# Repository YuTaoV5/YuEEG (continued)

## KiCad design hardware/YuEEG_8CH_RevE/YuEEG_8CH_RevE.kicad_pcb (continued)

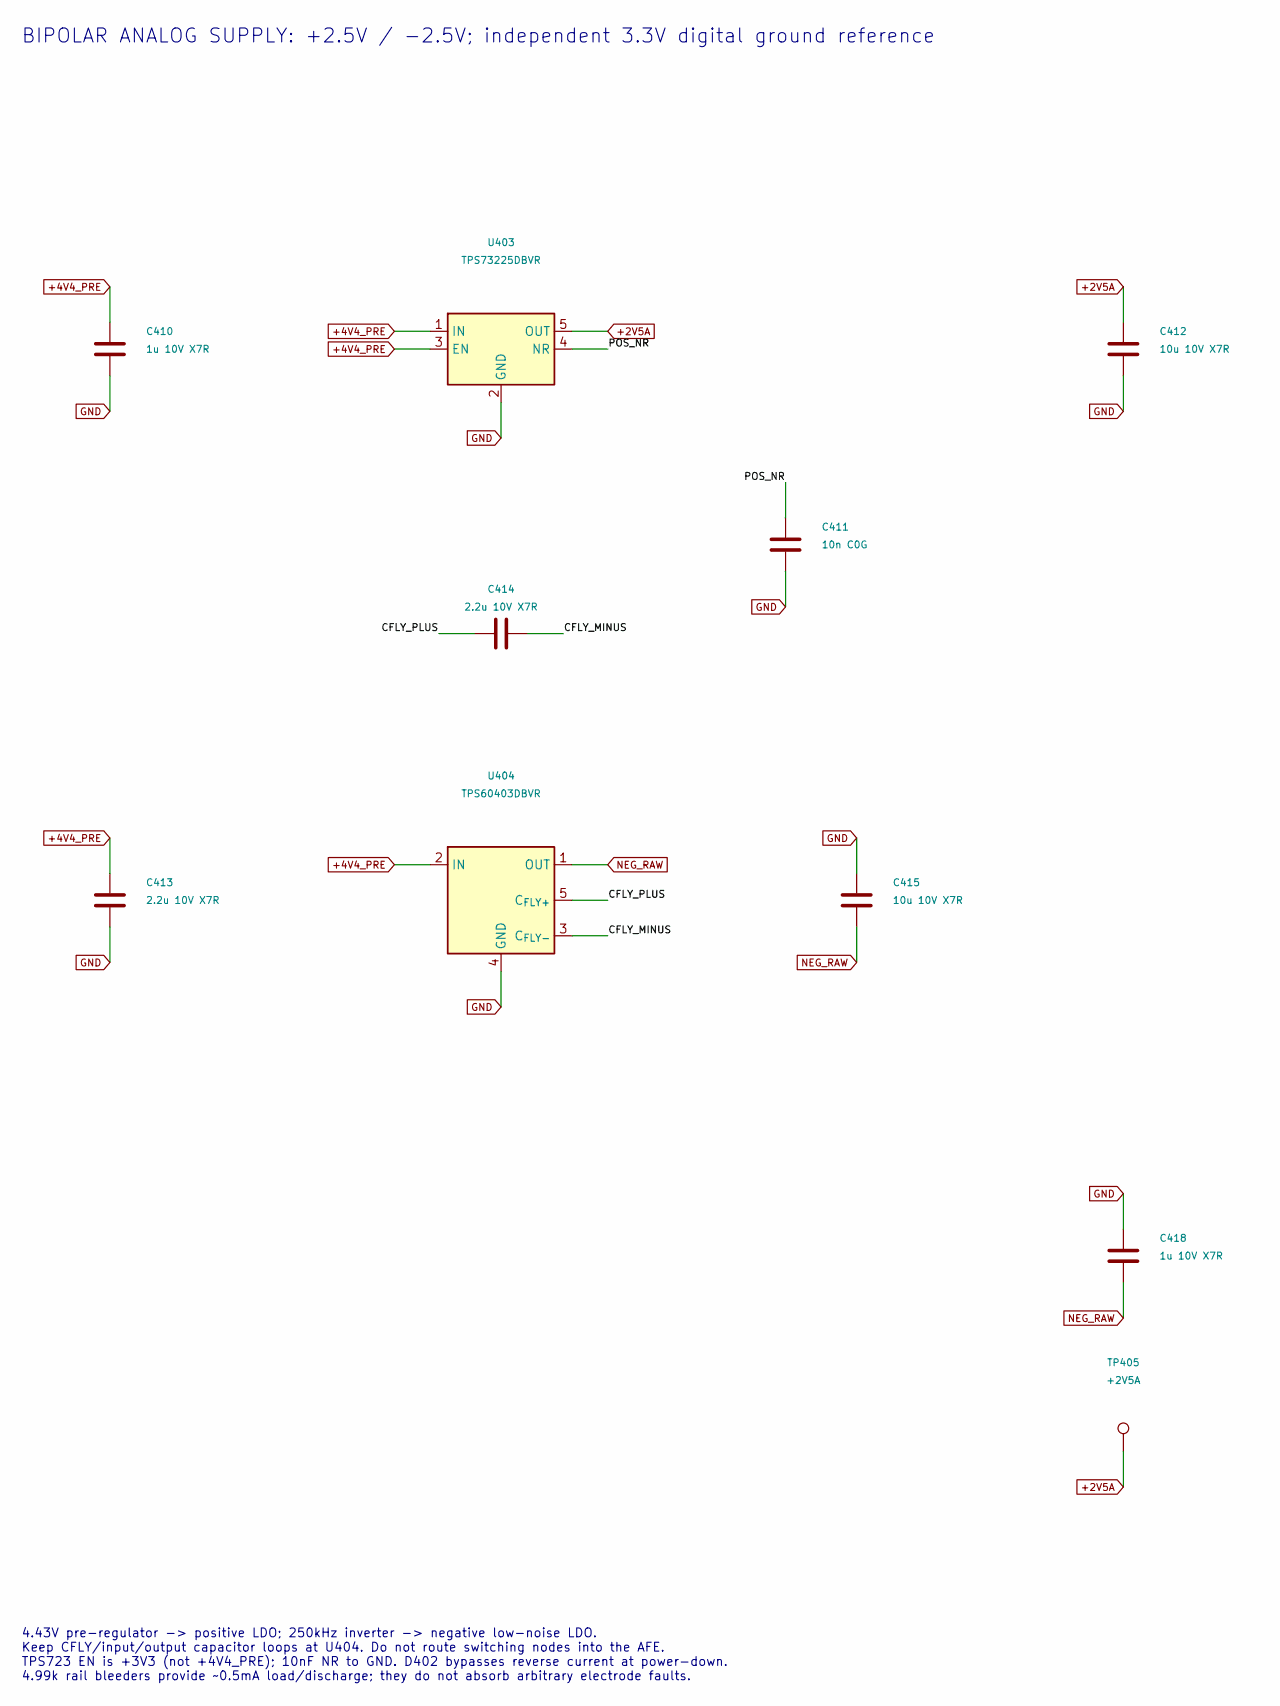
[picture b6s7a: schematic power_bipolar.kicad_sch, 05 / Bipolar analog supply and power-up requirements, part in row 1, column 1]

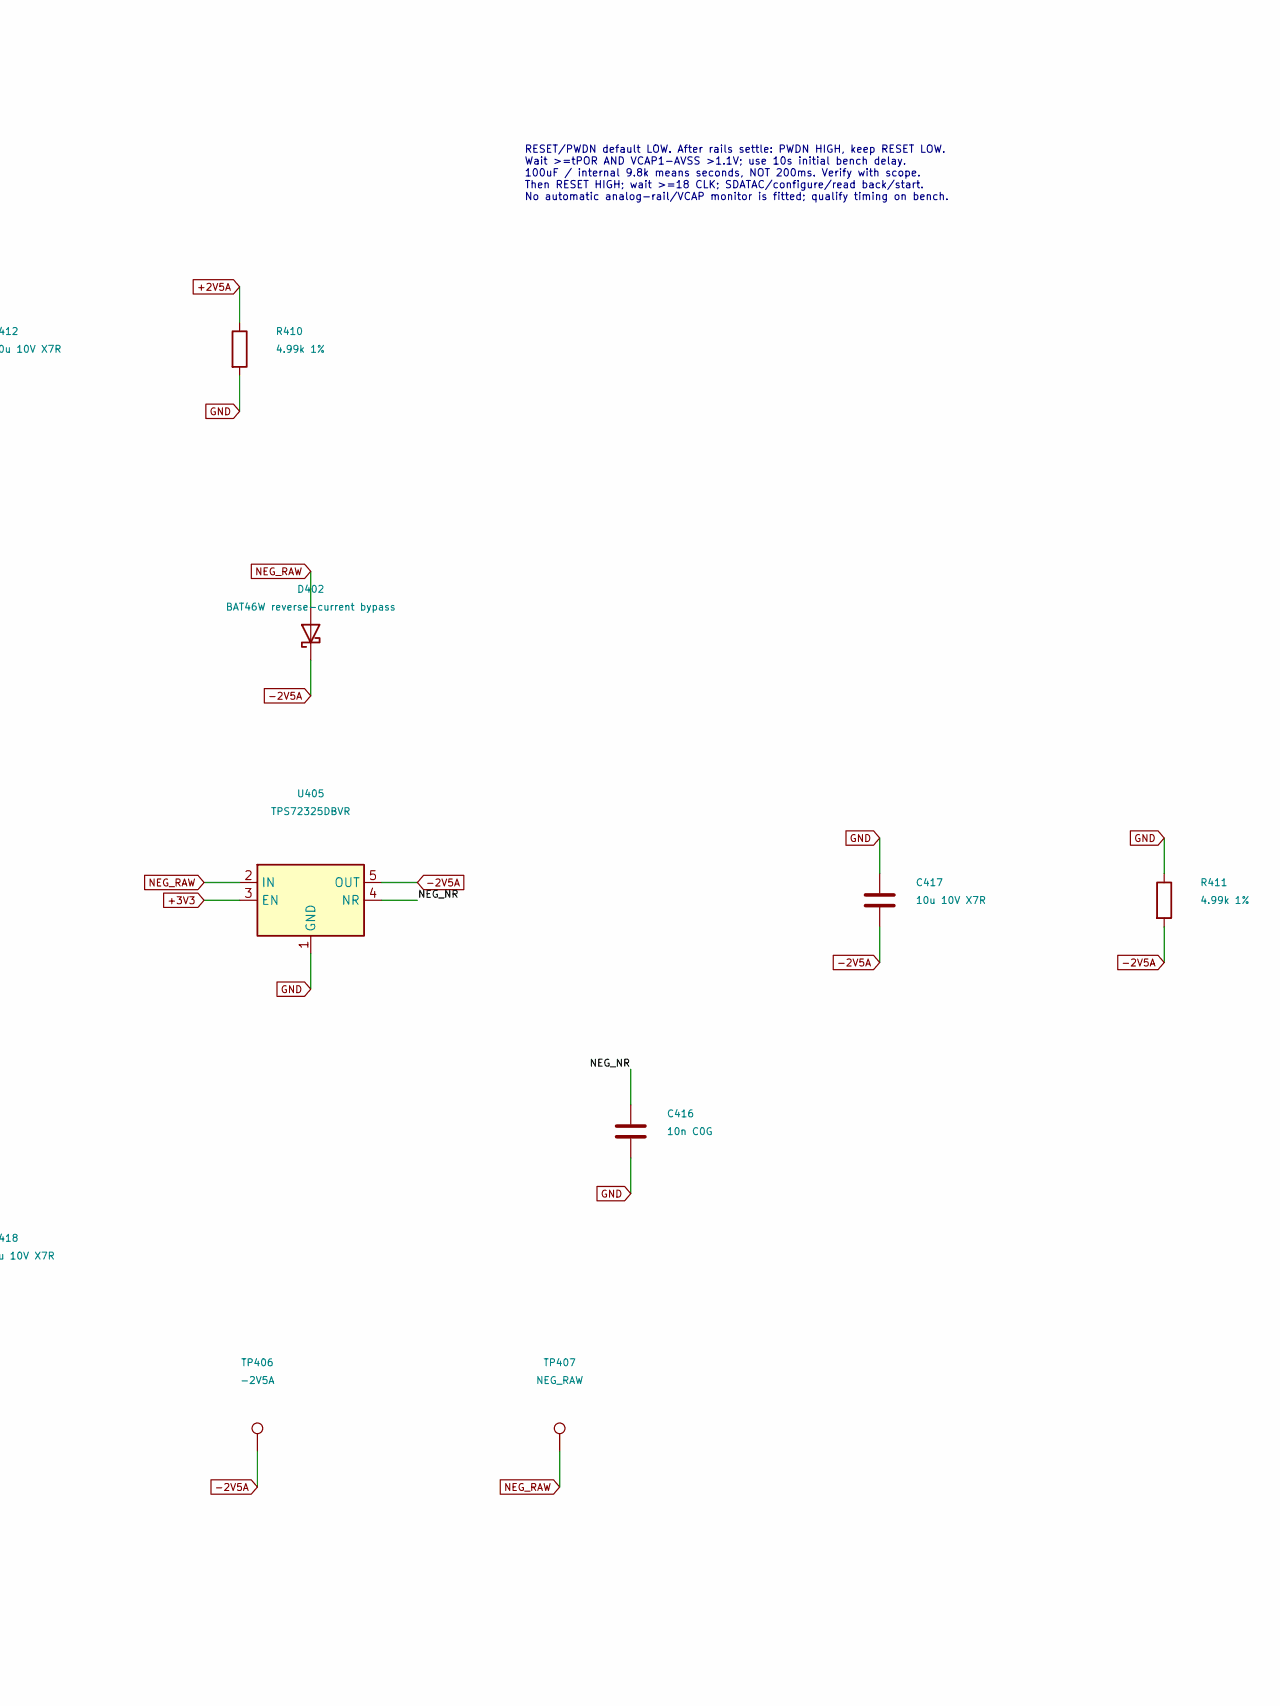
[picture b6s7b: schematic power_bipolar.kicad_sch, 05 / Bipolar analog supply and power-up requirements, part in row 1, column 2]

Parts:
C410, C418: 1u 10V X7R; C_0603_1608Metric
C411, C416: 10n C0G; C_0603_1608Metric
C412, C415, C417: 10u 10V X7R; C_0805_2012Metric
C413, C414: 2.2u 10V X7R; C_0805_2012Metric
D402: BAT46W reverse-current bypass; D_SOD-123
R410, R411: 4.99k 1%; R_0603_1608Metric
TP405: +2V5A; TestPoint_Pad_D1.5mm
TP406: -2V5A; TestPoint_Pad_D1.5mm
TP407: NEG_RAW; TestPoint_Pad_D1.5mm
U403: TPS73225DBVR; SOT-23-5
U404: TPS60403DBVR; SOT-23-5
U405: TPS72325DBVR; SOT-23-5

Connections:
+2V5A: C412.1, R410.1, TP405.1, U403.5 (OUT); also elsewhere on the board
+3V3: U405.3 (EN); also elsewhere on the board
+4V4_PRE: C410.1, C413.1, U403.1 (IN), U403.3 (EN), U404.2 (IN); also elsewhere on the board
-2V5A: C417.2, D402.1 (K), R411.2, TP406.1, U405.5 (OUT); also elsewhere on the board
/05 / Bipolar analog supply/CFLY_MINUS: C414.2, U404.3 (C_{FLY-})
/05 / Bipolar analog supply/CFLY_PLUS: C414.1, U404.5 (C_{FLY+})
/05 / Bipolar analog supply/NEG_NR: C416.1, U405.4 (NR)
/05 / Bipolar analog supply/POS_NR: C411.1, U403.4 (NR)
GND: C410.2, C411.2, C412.2, C413.2, C415.1, C416.2, C417.1, C418.1, R410.2, R411.1, U403.2 (GND), U404.4 (GND), U405.1 (GND); also elsewhere on the board
NEG_RAW: C415.2, C418.2, D402.2 (A), TP407.1, U404.1 (OUT), U405.2 (IN)

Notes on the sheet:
BIPOLAR ANALOG SUPPLY: +2.5V / -2.5V; independent 3.3V digital ground reference
4.43V pre-regulator -> positive LDO; 250kHz inverter -> negative low-noise LDO. Keep CFLY/input/output capacitor loops at U404. Do not route switching nodes into the AFE. TPS723 EN is +3V3 (not +4V4_PRE); 10nF NR to GND. D402 bypasses reverse current at power-down. 4.99k rail bleeders provide ~0.5m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
RESET/PWDN default LOW. After rails settle: PWDN HIGH, keep RESET LOW. Wait >=tPOR AND VCAP1-AVSS >1.1V; use 10s initial bench delay. 100uF / internal 9.8k means seconds, NOT 200ms. Verify with scope. Then RESET HIGH; wait >=18 CLK; SDATAC/configure/read back/start. No automatic analog-rail/VCAP mo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

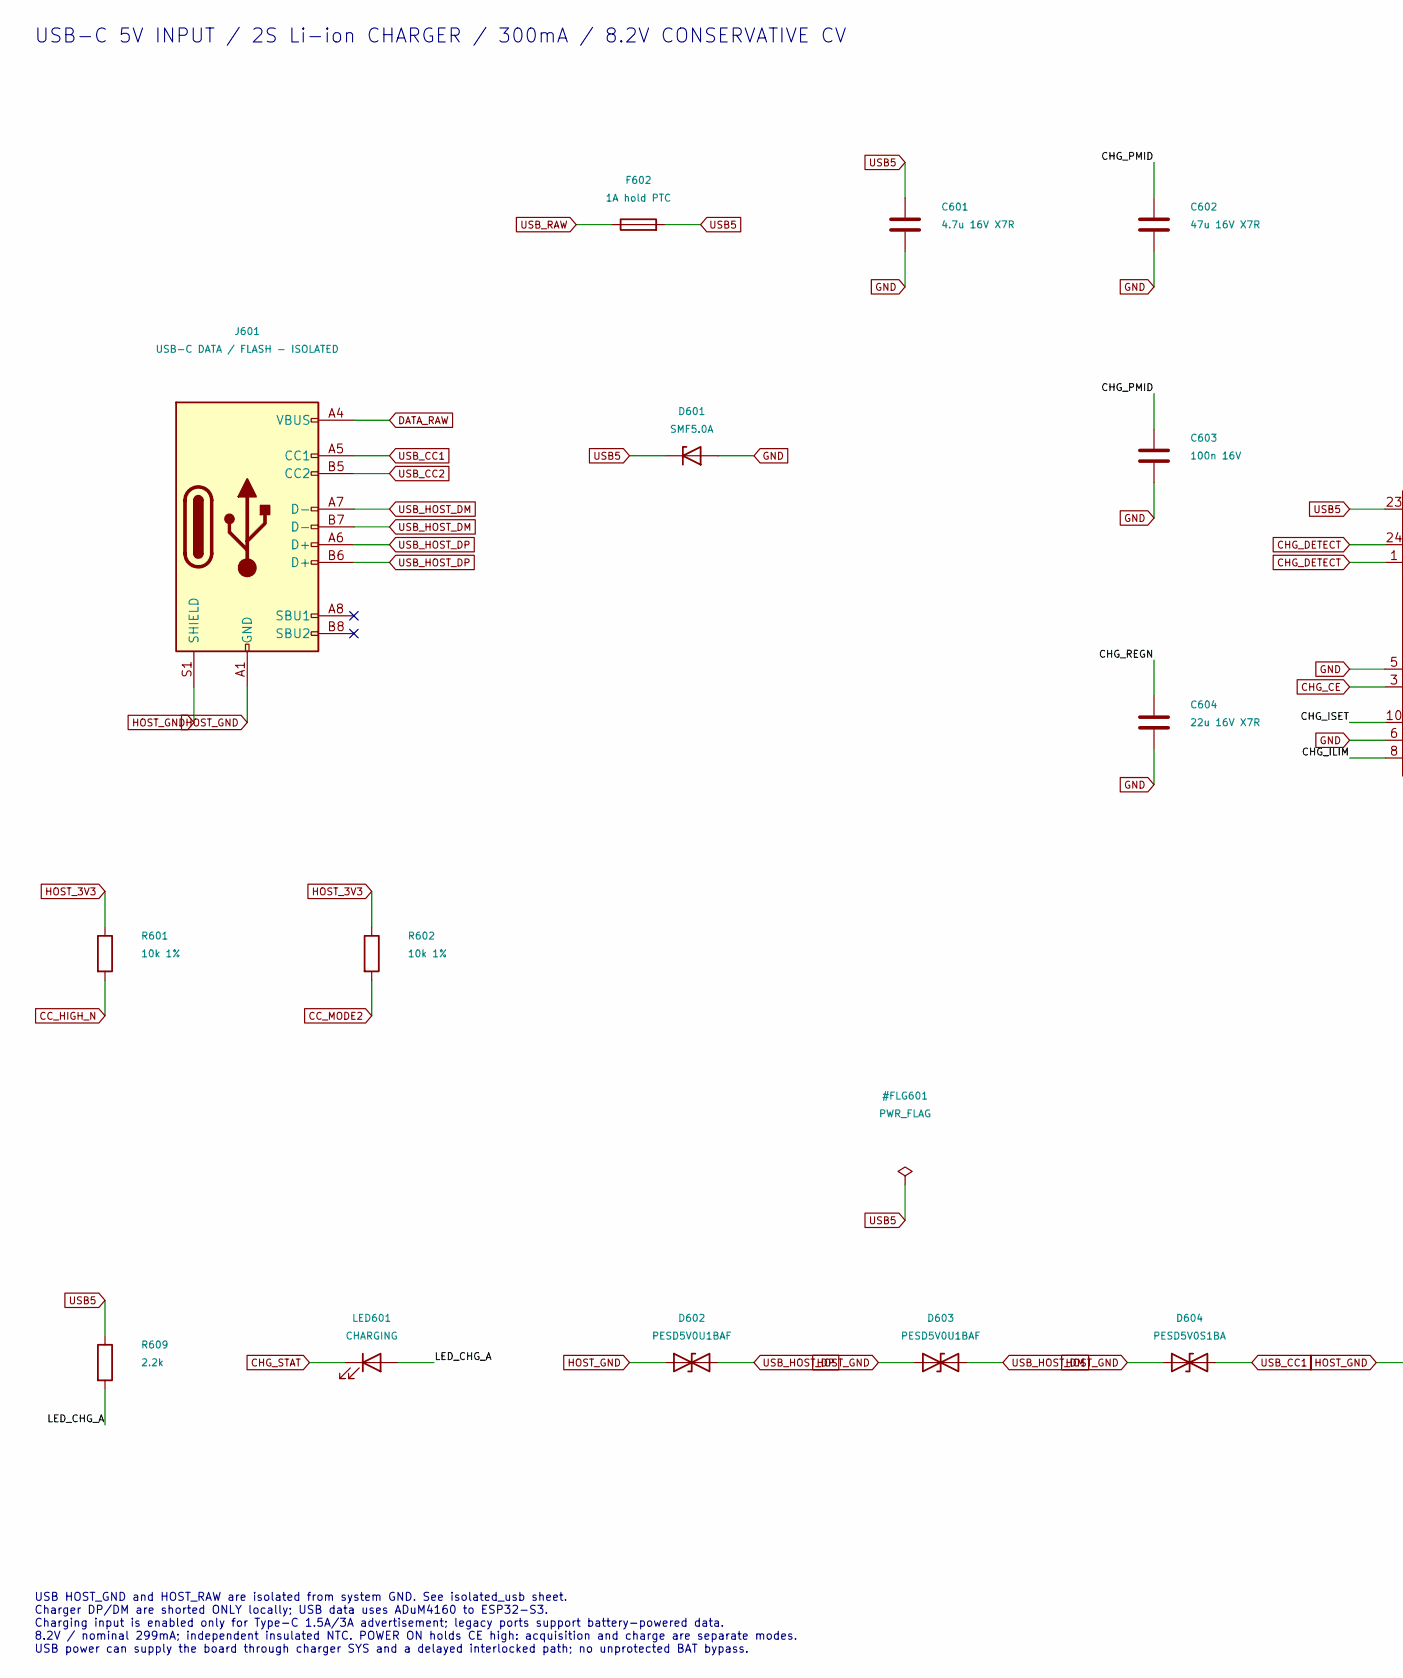
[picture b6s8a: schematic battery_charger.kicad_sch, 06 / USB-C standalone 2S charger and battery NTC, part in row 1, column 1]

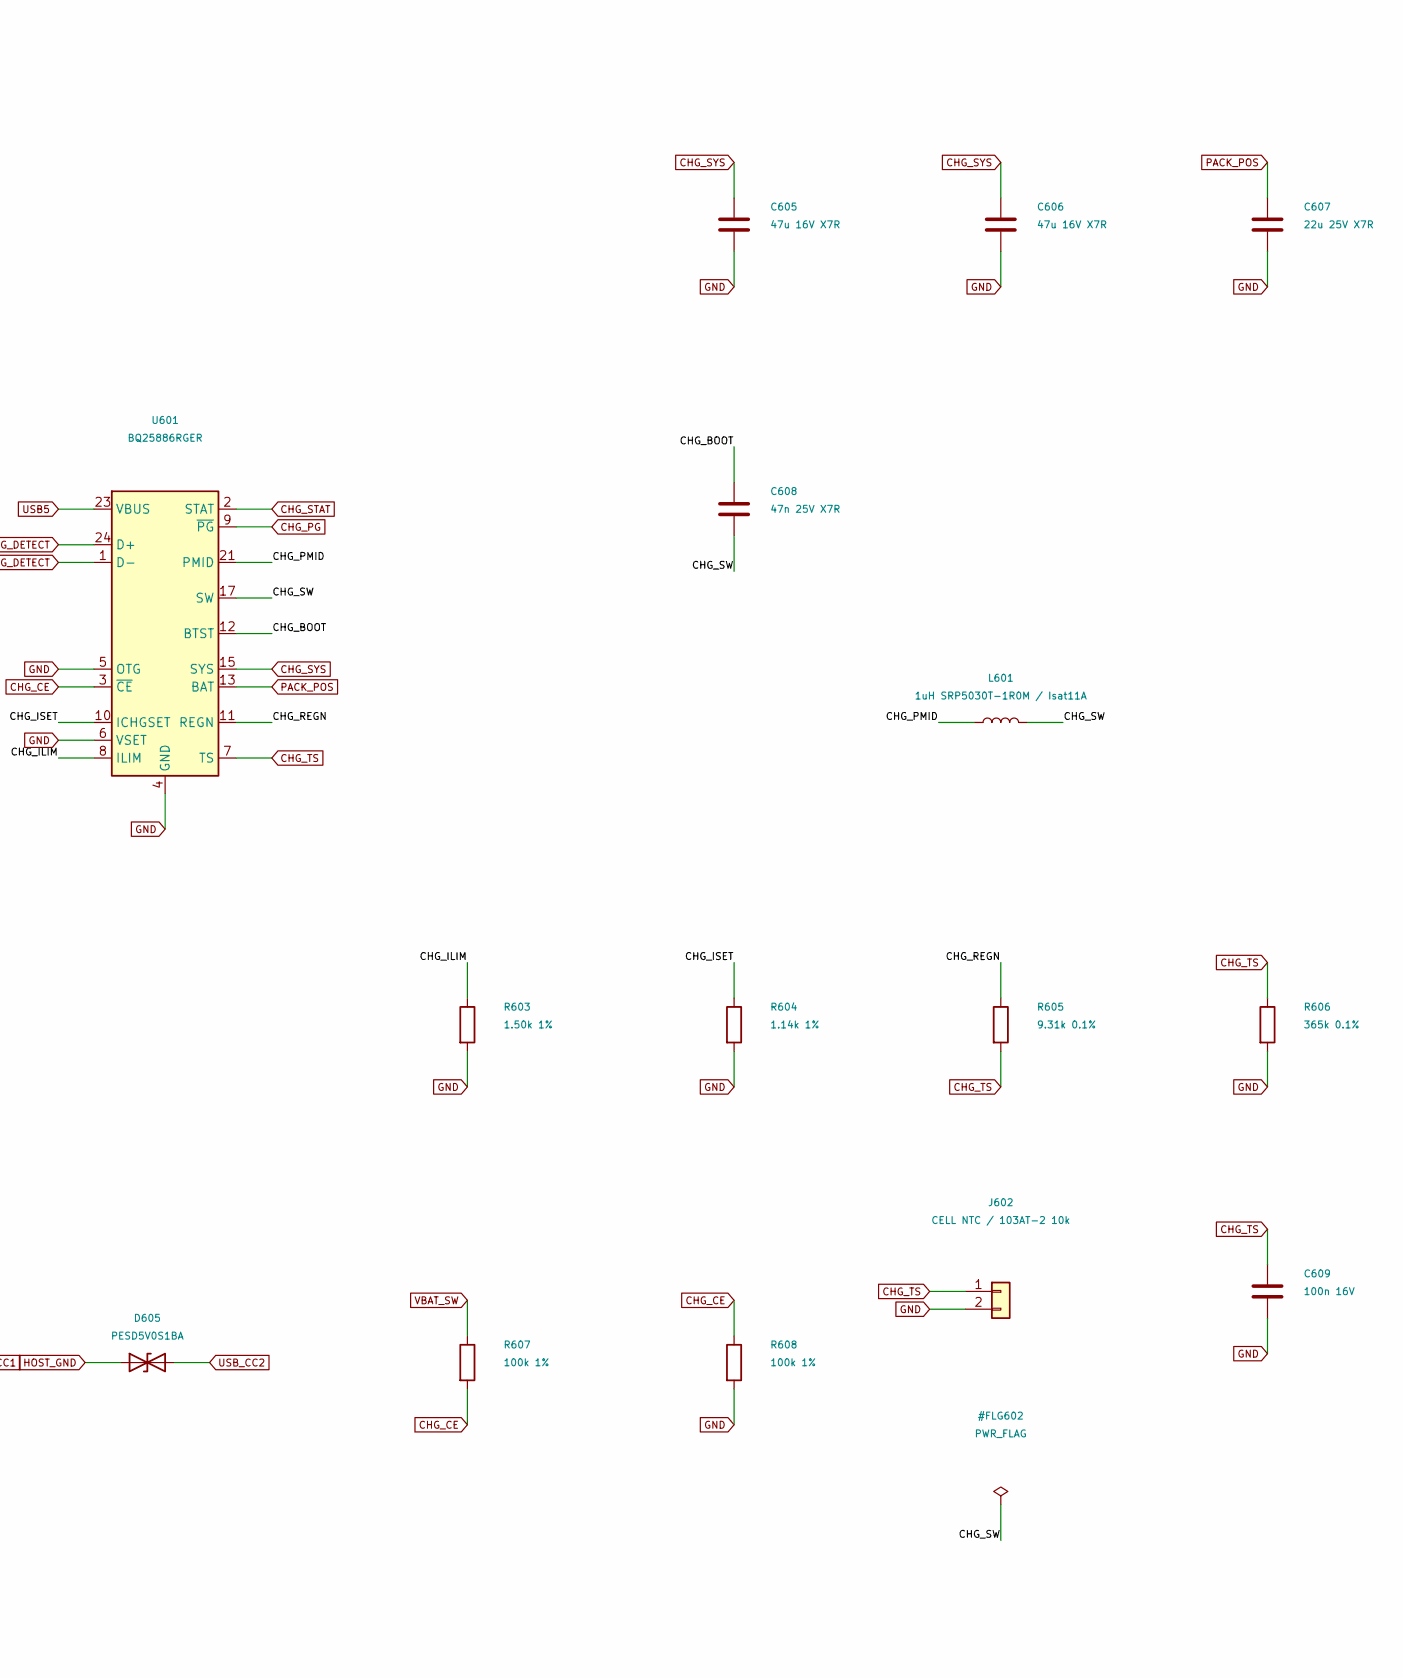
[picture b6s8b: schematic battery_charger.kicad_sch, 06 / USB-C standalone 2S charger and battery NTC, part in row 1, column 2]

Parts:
C601: 4.7u 16V X7R; C_0805_2012Metric
C602, C605, C606: 47u 16V X7R; C_1210_3225Metric
C603, C609: 100n 16V; C_0603_1608Metric
C604: 22u 16V X7R; C_1206_3216Metric
C607: 22u 25V X7R; C_1206_3216Metric
C608: 47n 25V X7R; C_0603_1608Metric
D601: SMF5.0A; D_SOD-123F
D602, D603: PESD5V0U1BAF; D_SOD-323
D604, D605: PESD5V0S1BA; D_SOD-323
F602: 1A hold PTC; Fuse_1206_3216Metric
J601: USB-C DATA / FLASH - ISOLATED; USB_C_Receptacle_HRO_TYPE-C-31-M-12
J602: CELL NTC / 103AT-2 10k; JST_PH_B2B-PH-K_1x02_P2.00mm_Vertical
L601: 1uH SRP5030T-1R0M / Isat11A; L_Bourns_SRP5030T
LED601: CHARGING; LED_0603_1608Metric
R601, R602: 10k 1%; R_0603_1608Metric
R603: 1.50k 1%; R_0603_1608Metric
R604: 1.14k 1%; R_0603_1608Metric
R605: 9.31k 0.1%; R_0603_1608Metric
R606: 365k 0.1%; R_0603_1608Metric
R607, R608: 100k 1%; R_0603_1608Metric
R609: 2.2k; R_0603_1608Metric
U601: BQ25886RGER; Texas_RGE0024H_VQFN-24-1EP_4x4mm_P0.5mm_EP2.7x2.7mm_Thermal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

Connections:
/06 / USB-C standalone 2S charger and battery NTC/CHG_BOOT: C608.1, U601.12 (BTST)
/06 / USB-C standalone 2S charger and battery NTC/CHG_ILIM: R603.1, U601.8 (ILIM)
/06 / USB-C standalone 2S charger and battery NTC/CHG_ISET: R604.1, U601.10 (ICHGSET)
/06 / USB-C standalone 2S charger and battery NTC/CHG_PMID: C602.1, C603.1, L601.1, U601.21 (PMID), U601.22 (PMID)
/06 / USB-C standalone 2S charger and battery NTC/CHG_REGN: C604.1, R605.1, U601.11 (REGN)
/06 / USB-C standalone 2S charger and battery NTC/CHG_SW: C608.2, L601.2, U601.17 (SW), U601.18 (SW)
/06 / USB-C standalone 2S charger and battery NTC/LED_CHG_A: LED601.2 (A), R609.2
CC_HIGH_N: R601.2; also elsewhere on the board
CC_MODE2: R602.2; also elsewhere on the board
CHG_CE: R607.2, R608.1, U601.3 (~CE)
CHG_DETECT: U601.1 (D-), U601.24 (D+)
CHG_PG: U601.9 (~PG); also elsewhere on the board
CHG_STAT: LED601.1 (K), U601.2 (STAT); also elsewhere on the board
CHG_SYS: C605.1, C606.1, U601.15 (SYS), U601.16 (SYS); also elsewhere on the board
CHG_TS: C609.1, J602.1, R605.2, R606.1, U601.7 (TS)
DATA_RAW: J601.A4 (VBUS), J601.A9 (VBUS), J601.B4 (VBUS), J601.B9 (VBUS); also elsewhere on the board
GND: C601.2, C602.2, C603.2, C604.2, C605.2, C606.2, C607.2, C609.2, D601.2 (A), J602.2, R603.2, R604.2, R606.2, R608.2, U601.4 (GND), U601.5 (OTG), U601.6 (VSET), U601.19 (GND), U601.20 (GND), U601.25 (GND); also elsewhere on the board
HOST_3V3: R601.1, R602.1; also elsewhere on the board
HOST_GND: D602.1 (A1), D603.1 (A1), D604.1 (A1), D605.1 (A1), J601.A1 (GND), J601.A12 (GND), J601.B1 (GND), J601.B12 (GND), J601.S1 (SHIELD); also elsewhere on the board
PACK_POS: C607.1, U601.13 (BAT), U601.14 (BAT); also elsewhere on the board
USB5: C601.1, D601.1 (K), F602.2, R609.1, U601.23 (VBUS); also elsewhere on the board
USB_CC1: D604.2 (A2), J601.A5 (CC1); also elsewhere on the board
USB_CC2: D605.2 (A2), J601.B5 (CC2); also elsewhere on the board
USB_HOST_DM: D603.2 (A2), J601.A7 (D-), J601.B7 (D-); also elsewhere on the board
USB_HOST_DP: D602.2 (A2), J601.A6 (D+), J601.B6 (D+); also elsewhere on the board
USB_RAW: F602.1; also elsewhere on the board
VBAT_SW: R607.1; also elsewhere on the board

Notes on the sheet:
USB-C 5V INPUT / 2S Li-ion CHARGER / 300mA / 8.2V CONSERVATIVE CV
USB HOST_GND and HOST_RAW are isolated from system GND. See isolated_usb sheet. Charger DP/DM are shorted ONLY locally; USB data uses ADuM4160 to ESP32-S3. Charging input is enabled only for Type-C 1.5A/3A advertisement; legacy ports support battery-powered data. 8.2V / nominal 299mA; independent i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

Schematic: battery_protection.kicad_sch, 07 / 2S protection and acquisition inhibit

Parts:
C620, C621, C640: 100n 16V; C_0603_1608Metric
C641: 10n C0G; C_0603_1608Metric
C642: 10n 25V; C_0603_1608Metric
D606, D607: BZT52C8V2S; D_SOD-323
F601: 1A fast fuse / 32V; Fuse_1206_3216Metric
J401: 2S RAW: B+ / MID / B-; JST_PH_B3B-PH-K_1x03_P2.00mm_Vertical
Q601: CSD17308Q3 DSG; VSON-8_3.3x3.3mm_P0.65mm_NexFET
Q602: CSD17308Q3 CHG; VSON-8_3.3x3.3mm_P0.65mm_NexFET
Q603, Q604: AO3401A BACK-TO-BACK; SOT-23
Q605: MMBT3904 ENABLE; SOT-23
Q606: MMBT3904 USB INHIBIT; SOT-23
R620, R621: 470R 1%; R_0603_1608Metric
R622: 2.00k 1%; R_0603_1608Metric
R623: 0.010R 1% 0.5W; R_1210_3225Metric
R640: 1.58M 0.1%; R_0603_1608Metric
R641, R643: 100k 0.1%; R_0603_1608Metric
R642: 2.05M 0.1%; R_0603_1608Metric
R644: 62k 1%; R_0603_1608Metric
R645: 10k; R_0603_1608Metric
R646, R648, R649: 1M; R_0603_1608Metric
R647, R651: 47k; R_0603_1608Metric
R650: 100k; R_0603_1608Metric
U602: S-8252AAY-M6T1U; SOT-23-6
U604: TPS3700DDCR RUN WINDOW; SOT-23-6

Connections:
/07 / Raw 2S cell protection and fail-safe acquisition switch/BMS_DRAINS: Q601.5 (D5-8_EP), Q602.5 (D5-8_EP)
/07 / Raw 2S cell protection and fail-safe acquisition switch/CHARGE_GATE: D607.1 (K), Q602.4 (G), U602.2 (CO)
/07 / Raw 2S cell protection and fail-safe acquisition switch/DSG_GATE: D606.1 (K), Q601.4 (G), U602.1 (DO)
/07 / Raw 2S cell protection and fail-safe acquisition switch/DSG_SOURCE: D606.2 (A), Q601.1 (S1), Q601.2 (S2), Q601.3 (S3), R623.2
/07 / Raw 2S cell protection and fail-safe acquisition switch/PROT_VC: C621.1, R621.2, U602.4 (VC)
/07 / Raw 2S cell protection and fail-safe acquisition switch/PROT_VDD: C620.1, R620.2, U602.5 (VDD)
/07 / Raw 2S cell protection and fail-safe acquisition switch/PROT_VM: R622.2, U602.3 (VM)
/07 / Raw 2S cell protection and fail-safe acquisition switch/RUN_GATE: C642.1, Q603.1 (G), Q604.1 (G), R649.2, R650.1
/07 / Raw 2S cell protection and fail-safe acquisition switch/RUN_NPN_BASE: Q605.1 (B), R645.2, R646.1
/07 / Raw 2S cell protection and fail-safe acquisition switch/RUN_OV: R642.2, R643.1, U604.4 (INB-)
/07 / Raw 2S cell protection and fail-safe acquisition switch/RUN_PULLDOWN: Q605.3 (C), R650.2
/07 / Raw 2S cell protection and fail-safe acquisition switch/RUN_SOURCES: C642.2, Q603.2 (S), Q604.2 (S), R649.1
/07 / Raw 2S cell protection and fail-safe acquisition switch/RUN_UV: C641.1, R640.2, R641.1, U604.3 (INA+)
/07 / Raw 2S cell protection and fail-safe acquisition switch/USB_INHIBIT_B: Q606.1 (B), R647.2, R648.1
ACQ_INPUT: Q604.3 (D), R651.1; also elsewhere on the board
GND: C640.2, C641.2, D607.2 (A), Q602.1 (S1), Q602.2 (S2), Q602.3 (S3), Q605.2 (E), Q606.2 (E), R622.1, R641.2, R643.2, R646.2, R648.2, R651.2, U604.2 (GND); also elsewhere on the board
PACK_POS: C640.1, F601.2, Q603.3 (D), R640.1, R642.1, R644.1, U604.5 (VDD); also elsewhere on the board
RAW_BMINUS: C620.2, C621.2, J401.3, R623.1, U602.6 (VSS); also elsewhere on the board
RAW_BPLUS: F601.1, J401.1, R620.1; also elsewhere on the board
RAW_MID: J401.2, R621.1; also elsewhere on the board
RUN_BASE: Q606.3 (C), R644.2, R645.1, U604.1 (OUTA), U604.6 (OUTB)
USB_RAW: R647.1; also elsewhere on the board

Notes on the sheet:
RAW CELL HARNESS: B+ / MID / B- ; NEVER SHORT RAW B- TO SYSTEM GND
Primary protection per cell: OV 4.25V / UV 3.00V; inhibit 0V-cell recharge. Charge/discharge overcurrent use VM and actual series resistance. Q601/Q602 are common-DRAIN NMOS. Q603/Q604 are common-SOURCE PMOS; no body-diode bypass when OFF. RUN typical falling cutoff ~6.63V, restart ~6.72V, OV cutof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

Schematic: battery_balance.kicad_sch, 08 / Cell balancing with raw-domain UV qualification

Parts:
C630, C631, C632, C660: 100n 16V; C_0603_1608Metric
C633: 330n 16V; C_0603_1608Metric
Q607: 2N7002 RAW UV GATE; SOT-23
R630: 160R 1%; R_0603_1608Metric
R631: 260R 1%; R_0603_1608Metric
R632, R633: 100R 1%; R_0603_1608Metric
R634: 330k; R_0603_1608Metric
R660: 1.81M 0.1%; R_0603_1608Metric
R661: 100k 0.1%; R_0603_1608Metric
R662: 1M; R_0603_1608Metric
R663: 2.2k; R_0603_1608Metric
TP601: RAW_BPLUS; TestPoint_Pad_D1.5mm
TP602: RAW_MID; TestPoint_Pad_D1.5mm
TP603: RAW_BMINUS; TestPoint_Pad_D1.5mm
TP604: BAL_OV_ALARM; TestPoint_Pad_D1.5mm
TP605: CHG_PG; TestPoint_Pad_D1.5mm
TP606: CHG_STAT; TestPoint_Pad_D1.5mm
U603: BQ29209DRBR; VSON-8-1EP_3x3mm_P0.65mm_EP1.6x2.4mm
U605: TPS3700DDCR BAL UV; SOT-23-6
U606: LTV-356T VALID USB; SO-4_4.4x3.6mm_P2.54mm

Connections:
/08 / Cell balancing with raw-domain UV qualification/BAL_AND_SOURCE: Q607.3 (D), U606.3
/08 / Cell balancing with raw-domain UV qualification/BAL_CD: C633.1, U603.4 (CD)
/08 / Cell balancing with raw-domain UV qualification/BAL_OPTO_A: R663.2, U606.1
/08 / Cell balancing with raw-domain UV qualification/BAL_OV_ALARM: TP604.1, U603.8 (OUT)
/08 / Cell balancing with raw-domain UV qualification/BAL_UV_SENSE: R660.2, R661.1, U605.3 (INA+)
/08 / Cell balancing with raw-domain UV qualification/BAL_VC1: C631.2, C632.1, R631.2, U603.2 (VC1)
/08 / Cell balancing with raw-domain UV qualification/BAL_VC1_CB: R632.2, U603.3 (VC1_CB)
/08 / Cell balancing with raw-domain UV qualification/BAL_VC2: C631.1, R630.2, U603.1 (VC2)
BAL_ENABLE: R634.2, U603.6 (CB_EN), U606.4
BAL_VDD: C630.1, R633.2, R634.1, U603.7 (VDD)
CHG_PG: TP605.1, U606.2; also elsewhere on the board
CHG_STAT: TP606.1; also elsewhere on the board
RAW_BMINUS: C630.2, C632.2, C633.2, C660.2, Q607.2 (S), R661.2, TP603.1, U603.5 (GND), U603.9 (EP), U605.2 (GND), U605.4 (INB-); also elsewhere on the board
RAW_BPLUS: C660.1, R630.1, R633.1, R660.1, R662.1, TP601.1, U605.5 (VDD); also elsewhere on the board
RAW_MID: R631.1, R632.1, TP602.1; also elsewhere on the board
RAW_OK: Q607.1 (G), R662.2, U605.1 (OUTA)
USB5: R663.1; also elsewhere on the board

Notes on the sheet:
CELL BALANCING: ONLY WITH VALID USB SOURCE AND RAW PACK ABOVE ~7.6V
BQ29209 internal balancing: TI Fig9 resistor network, about 10mA; matched cells required. Not a cell equalizer for mismatched/old cells. VC2 capacitor returns to VC1; VC1 capacitor returns to RAW B-. Do not return raw-domain nodes to system GND. CB_EN active LOW: 330k pull-up disables by default. O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

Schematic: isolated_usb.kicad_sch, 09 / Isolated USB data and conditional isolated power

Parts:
C701, C702, C703, C706, C707, C709: 100n 16V; C_0603_1608Metric
C704: 1u 16V; C_0603_1608Metric
C705: 1u 10V; C_0603_1608Metric
C708: 4.7u 16V; C_0603_1608Metric
C710: 10u 25V X7R; C_1206_3216Metric
D701: SMF5.0A; D_SOD-123F
F701: 1.5A hold PTC; Fuse_1206_3216Metric
R701, R702, R703, R704: 24R 1%; R_0603_1608Metric
R705: 887k 1%; R_0603_1608Metric
R706: 23.7k 1%; R_0603_1608Metric
R707: 100k; R_0603_1608Metric
U701: ADuM4160BRIZ / enhanced creepage; ADuM4160_RI16_8p5gap
U702: TLV75533PDBVR HOST ONLY; SOT-23-5
U703: TUSB320LAIRWBR / UFP GPIO; Texas_X2QFN-12_1.6x1.6mm_P0.4mm
U704: SN74LVC1G04DBVR; SOT-23-5
U705: TPS2553DBVR; SOT-23-6
U706: THM 6-0511 / standard pinout; THM6_Standard

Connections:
+3V3: C703.1, U701.12 (PIN), U701.13 (SPD), U701.14 (VDD2), U701.16 (VBUS2); also elsewhere on the board
/09 / Isolated USB data and conditional isolated power/CC_VBUS_DET: R705.2, U703.4 (VBUS_DET)
/09 / Isolated USB data and conditional isolated power/HOST_DCDC_IN: C708.1, U705.6 (OUT), U706.1 (+VIN)
/09 / Isolated USB data and conditional isolated power/HOST_ILIM: R706.1, U705.5 (ILIM)
/09 / Isolated USB data and conditional isolated power/HOST_POWER_EN: R707.1, U704.4 (Y), U705.3 (EN)
/09 / Isolated USB data and conditional isolated power/USB_DOWN_DM: R704.1, U701.11 (DD-)
/09 / Isolated USB data and conditional isolated power/USB_DOWN_DP: R703.1, U701.10 (DD+)
/09 / Isolated USB data and conditional isolated power/USB_UP_DM: R702.2, U701.6 (UD-)
/09 / Isolated USB data and conditional isolated power/USB_UP_DP: R701.2, U701.7 (UD+)
/09 / Isolated USB data and conditional isolated power/USB_VDD1: C702.1, U701.3 (VDD1), U701.4 (PDEN), U701.5 (SPU)
CC_HIGH_N: U703.7 (OUT1), U704.2 (A); also elsewhere on the board
CC_MODE2: U703.8 (OUT2); also elsewhere on the board
CHARGE_CC1: U703.1 (CC1); also elsewhere on the board
CHARGE_CC2: U703.2 (CC2); also elsewhere on the board
DATA_5V: C701.1, U701.1 (VBUS1); also elsewhere on the board
GND: C703.2, C710.2, U701.9 (GND2), U701.15 (GND2), U706.12 (-VOUT); also elsewhere on the board
HOST_3V3: C705.1, C706.1, C707.1, U702.5 (OUT), U703.12 (VDD), U704.5 (VCC); also elsewhere on the board
HOST_5V: C704.1, C709.1, D701.1 (K), F701.2, R705.1, U702.1 (IN), U702.3 (EN), U705.1 (IN)
HOST_GND: C701.2, C702.2, C704.2, C705.2, C706.2, C707.2, C708.2, C709.2, D701.2 (A), R706.2, R707.2, U701.2 (GND1), U701.8 (GND1), U702.2 (GND), U703.3 (PORT_UFP), U703.10 (GND), U703.11 (EN_N), U704.3 (GND), U705.2 (GND), U706.23 (-VIN), U706.24 (-VIN); also elsewhere on the board
HOST_RAW: F701.1; also elsewhere on the board
USB_HOST_DM: R702.1; also elsewhere on the board
USB_HOST_DP: R701.1; also elsewhere on the board
USB_MCU_DM: R704.2; also elsewhere on the board
USB_MCU_DP: R703.2; also elsewhere on the board
USB_RAW: C710.1, U706.13 (+VOUT); also elsewhere on the board

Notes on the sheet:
HOST SIDE: NO ELECTRODE / SYSTEM GROUND CONNECTION
ADuM4160 BRIZ: full-speed 12Mbps; both speed pins HIGH. 24R series on all four USB lines. Primary CC controller replaces external Rd resistors. OUT1 LOW only for advertised 1.5A/3A. TPS2553 RILIM=23.7k: max about 1.17A before resistor tolerance; no PD negotiation. THM6 standard pinout only, not -B1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

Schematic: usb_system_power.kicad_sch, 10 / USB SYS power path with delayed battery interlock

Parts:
C711: 47n 10% 25V; C_0603_1608Metric
C712: 100n 16V; C_0603_1608Metric
C713: 10n 25V; C_0603_1608Metric
Q701, Q702: AO3401A USB BACK-TO-BACK; SOT-23
Q703: MMBT3904 USB ENABLE; SOT-23
R710: 1.00M 0.1%; R_0603_1608Metric
R711: 100k 0.1%; R_0603_1608Metric
R712, R716: 100k; R_0603_1608Metric
R713: 47k; R_0603_1608Metric
R714, R715: 1M; R_0603_1608Metric
U707: TPS3808G01DBVR; SOT-23-6

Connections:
ACQ_INPUT: Q702.3 (D); also elsewhere on the board
CHG_SYS: Q701.3 (D); also elsewhere on the board
GND: C711.2, C712.2, Q703.2 (E), R711.2, R714.2, U707.2 (GND); also elsewhere on the board
USB_RAW: C712.1, R710.1, R712.1, U707.3 (MR), U707.6 (VDD); also elsewhere on the board
USB_RUN_BASE: Q703.1 (B), R713.2, R714.1
USB_RUN_CT: C711.1, U707.4 (CT)
USB_RUN_GATE: C713.1, Q701.1 (G), Q702.1 (G), R715.2, R716.1
USB_RUN_READY: R712.2, R713.1, U707.1 (RESET)
USB_RUN_SENSE: R710.2, R711.1, U707.5 (SENSE)
USB_RUN_SINK: Q703.3 (C), R716.2
USB_RUN_SOURCE: C713.2, Q701.2 (S), Q702.2 (S), R715.1

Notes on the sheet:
USB DATA + WIFI MAY RUN TOGETHER; CHARGING IS DISABLED WHILE POWER IS ON
USB_RAW rising above about 4.455V must remain valid for about 0.2s before USB SYS path turns ON. Existing battery path is inhibited immediately by Q606 sensing isolated USB_RAW. Delayed USB turn-on avoids a parallel charge path. USB_RAW falling trips supervisor while Q606 still inhibits the battery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

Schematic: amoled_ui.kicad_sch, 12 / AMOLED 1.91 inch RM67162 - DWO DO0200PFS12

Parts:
C1001: 1n 25V; C_0603_1608Metric
C1002, C1010: 22u 10V X7R; C_1206_3216Metric
C1003, C1008, C1009, C1012: 100n 10V; C_0603_1608Metric
C1004, C1006, C1011: 1u 10V; C_0603_1608Metric
C1005, C1007: 4.7u 10V; C_0603_1608Metric
J1001: DO0200PFS12 18-PIN HARNESS; Molex_Panelmate_53780-1870_1x18-1MP_P1.25mm_Horizontal
Q1001: MMBT3904 OE ENABLE; SOT-23
R1001, R1004: 100k; R_0603_1608Metric
R1002, R1006: 10k; R_0603_1608Metric
R1003: 1k; R_0603_1608Metric
R1005: 1M; R_0603_1608Metric
R1021, R1022, R1023, R1024, R1025, R1026, R1027: 22R; R_0603_1608Metric
R1031, R1032, R1033, R1034, R1035, R1036, R1037: 47k; R_0603_1608Metric
U1001: TPS22918DBVR AMOLED POWER; SOT-23-6
U1002: TPS7A2028PDBVR; SOT-23-5
U1003: TPS7A2018PDBVR; SOT-23-5
U1004: SN74AXC8T245PWR / 3V3 -> 1V8; TSSOP-24_4.4x7.8mm_P0.65mm

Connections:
+3V3: C1003.1, C1008.1, R1002.1, R1031.1, U1001.1 (VIN), U1004.1 (VCCA), U1004.2 (DIR1), U1004.11 (DIR2); also elsewhere on the board
AM_1V8: C1007.1, C1009.1, C1012.1, J1001.3, R1006.1, U1003.5 (OUT), U1004.23 (VCCB), U1004.24 (VCCB)
AM_2V8: C1005.1, C1011.1, J1001.2, U1002.5 (OUT)
AM_CLK_A: R1032.2, U1004.4 (A2); also elsewhere on the board
AM_CLK_B: R1022.1, U1004.20 (B2)
AM_CLK_P: J1001.6, R1022.2
AM_CS_A: R1031.2, U1004.3 (A1); also elsewhere on the board
AM_CS_B: R1021.1, U1004.21 (B1)
AM_CS_P: J1001.5, R1021.2
AM_CT: C1001.1, U1001.4 (CT)
AM_D0_A: R1033.2, U1004.5 (A3); also elsewhere on the board
AM_D0_B: R1023.1, U1004.19 (B3)
AM_D0_P: J1001.7, R1023.2
AM_D1_A: R1034.2, U1004.6 (A4); also elsewhere on the board
AM_D1_B: R1024.1, U1004.18 (B4)
AM_D1_P: J1001.8, R1024.2
AM_D2_A: R1035.2, U1004.7 (A5); also elsewhere on the board
AM_D2_B: R1025.1, U1004.17 (B5)
AM_D2_P: J1001.9, R1025.2
AM_D3_A: R1036.2, U1004.8 (A6); also elsewhere on the board
AM_D3_B: R1026.1, U1004.16 (B6)
AM_D3_P: J1001.10, R1026.2
AM_IM1: J1001.16, R1006.2
AM_OE_BASE: Q1001.1 (B), R1004.2, R1005.1
AM_OE_N: Q1001.3 (C), R1002.2, U1004.22 (OE_N)
AM_POWER_EN: R1001.1, R1004.1, U1001.3 (ON); also elsewhere on the board
AM_QOD: R1003.2, U1001.5 (QOD)
AM_RAW: C1002.1, C1004.1, C1006.1, C1010.1, J1001.1, R1003.1, U1001.6 (VOUT), U1002.1 (IN), U1002.3 (EN), U1003.1 (IN), U1003.3 (EN)
AM_RST_A: R1037.2, U1004.9 (A7); also elsewhere on the board
AM_RST_B: R1027.1, U1004.15 (B7)
AM_RST_P: J1001.11, R1027.2
GND: C1001.2, C1002.2, C1003.2, C1004.2, C1005.2, C1006.2, C1007.2, C1008.2, C1009.2, C1010.2, C1011.2, C1012.2, J1001.12, J1001.18, Q1001.2 (E), R1001.2, R1005.2, R1032.1, R1033.1, R1034.1, R1035.1, R1036.1, R1037.1, U1001.2 (GND), U1002.2 (GND), U1003.2 (GND), U1004.10 (A8), U1004.12 (GND), U1004.13 (GND); also elsewhere on the board

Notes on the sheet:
12 / AMOLED 1.91 INCH RM67162 - DWO DO0200PFS12
Lock RM67162 version; module R4=0R, R3=NC, IM1 high for QSPI. VBAT=AM_RAW; VCC=2.8V; IOVCC=1.8V. Touch held in RESET; touch signals and TE unused. 18-core harness pin numbering must match vendor CN1. Keep screen and harness in floating system domain. Driver starts at 10MHz; refresh limited to statu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

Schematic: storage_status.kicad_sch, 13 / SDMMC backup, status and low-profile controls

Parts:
C1101: 22u 10V X7R; C_1206_3216Metric
C1102: 100n 10V; C_0603_1608Metric
C1103: 1u 10V; C_0603_1608Metric
C1120: 10n 10V; C_0603_1608Metric
D1101, D1102: USBLC6-2SC6; SOT-23-6
FB1101: BLM18PG121SN1D / 120R@100MHz; R_0603_1608Metric
H1001, H1002, H1003, H1004: AMOLED M2 / 6mm STANDOFF; MountingHole_2.2mm_M2
J1101: HIROSE DM3AT-SF-PEJM5; microSD_HC_Hirose_DM3AT-SF-PEJM5
LED801: POWER; LED_0603_1608Metric
LED802: RUN; LED_0603_1608Metric
LED803: WIFI; LED_0603_1608Metric
LED804: FAULT; LED_0603_1608Metric
R840, R841, R842, R843: 2.2k; R_0603_1608Metric
R1101: 22R; R_0603_1608Metric
R1111, R1112, R1113, R1114, R1115, R1116, R1120: 10k; R_0603_1608Metric
SW1001: EVPBB2A9B000 / REC; EVPBB_2p6x1p6_H0p53

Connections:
+3V3: FB1101.1, R840.1, R841.1, R842.1, R843.1, R1120.1; also elsewhere on the board
GND: C1101.2, C1102.2, C1103.2, C1120.2, D1101.2 (GND), D1102.2 (GND), J1101.6 (VSS), J1101.10 (CD2), J1101.11 (SHIELD), LED801.1 (K), SW1001.2; also elsewhere on the board
KEY_REC: C1120.1, R1120.2, SW1001.1; also elsewhere on the board
LED_FAULT_K: LED804.1 (K); also elsewhere on the board
LED_RUN_K: LED802.1 (K); also elsewhere on the board
LED_WIFI_K: LED803.1 (K); also elsewhere on the board
SD_3V3: C1101.1, C1102.1, C1103.1, D1101.5 (VBUS), D1102.5 (VBUS), FB1101.2, J1101.4 (VDD), R1111.1, R1112.1, R1113.1, R1114.1, R1115.1, R1116.1
SD_CD: D1102.3 (IO2), D1102.4 (IO2), J1101.9 (CD1), R1116.2; also elsewhere on the board
SD_CLK_CARD: D1101.1 (IO1), D1101.6 (IO1), J1101.5 (CLK), R1101.2
SD_CLK_HOST: R1101.1; also elsewhere on the board
SD_CMD: D1101.3 (IO2), D1101.4 (IO2), J1101.3 (CMD), R1111.2; also elsewhere on the board
SD_D0: D1102.1 (IO1), D1102.6 (IO1), J1101.7 (DAT0), R1112.2; also elsewhere on the board
SD_DAT1: J1101.8 (DAT1), R1113.2
SD_DAT2: J1101.1 (DAT2), R1114.2
SD_DAT3: J1101.2 (DAT3), R1115.2
STATUS_FAULT_A: LED804.2 (A), R843.2
STATUS_POWER_A: LED801.2 (A), R840.2
STATUS_RUN_A: LED802.2 (A), R841.2
STATUS_WIFI_A: LED803.2 (A), R842.2

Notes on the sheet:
13 / SDMMC BACKUP, STATUS AND LOW-PROFILE CONTROLS
1-bit SDMMC: CMD and DAT0..3 each have 10k pull-ups, including unused DAT1/2/3. CLK has source series termination. No SD, display or network IO in DRDY ISR. Separate recording ring and explicit drop counters; no lossless claim. REC key toggles EEG start/stop after debounce. BOOT/RESET remain hardwa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

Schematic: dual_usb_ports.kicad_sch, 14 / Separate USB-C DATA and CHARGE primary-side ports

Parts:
C901: 100n 16V; C_0603_1608Metric
D901: SMF5.0A DATA VBUS; D_SOD-123F
D902, D903: PESD5V0S1BA; D_SOD-323
F901: 500mA HOLD PTC; Fuse_1206_3216Metric
J901: USB-C CHARGE / POWER - NO DATA; USB_C_Receptacle_HRO_TYPE-C-31-M-12
R901, R902: 5.1k 1%; R_0603_1608Metric

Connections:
CHARGE_CC1: D902.1 (A1), J901.A5 (CC1); also elsewhere on the board
CHARGE_CC2: D903.1 (A1), J901.B5 (CC2); also elsewhere on the board
DATA_5V: C901.1, D901.1 (A1), F901.2; also elsewhere on the board
DATA_RAW: F901.1; also elsewhere on the board
HOST_GND: C901.2, D901.2 (A2), D902.2 (A2), D903.2 (A2), J901.A1 (GND), J901.A12 (GND), J901.B1 (GND), J901.B12 (GND), J901.S1 (SHIELD), R901.2, R902.2; also elsewhere on the board
HOST_RAW: J901.A4 (VBUS), J901.A9 (VBUS), J901.B4 (VBUS), J901.B9 (VBUS); also elsewhere on the board
USB_CC1: R901.1; also elsewhere on the board
USB_CC2: R902.1; also elsewhere on the board

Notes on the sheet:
14 / SEPARATE USB-C DATA AND CHARGE PRIMARY-SIDE PORTS
J601 DATA supplies only ADuM upstream side through F901. It cannot charge or power the acquisition domain. J901 CHARGE supplies existing F701 / CC current detector / isolated DC-DC chain. D+/D- are NC. No DATA_RAW/DATA_5V to HOST_RAW/HOST_5V connection or diode OR. Both ports share only HOST_GND an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
